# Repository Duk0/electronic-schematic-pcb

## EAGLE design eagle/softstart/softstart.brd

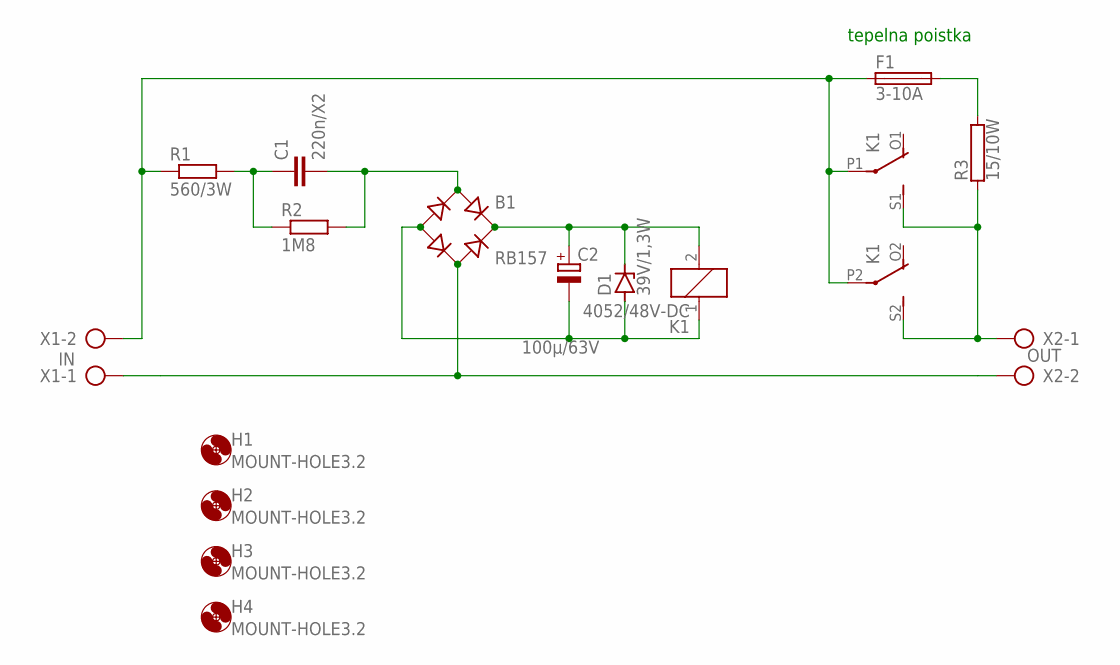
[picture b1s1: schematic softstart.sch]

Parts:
B1: RB157; RB1A
C1: 220n/X2; C150-072X183
C2: 100µ/63V; E5-10,5
D1: 39V/1,3W; DO35Z10
F1: 3-10A; TE5
H1, H2, H3, H4: MOUNT-HOLE3.2; 3,2
K1: 4052/48V-DC; F4052
R1: 560/3W; 0617/22
R2: 1M8; 0207/10
R3: 15/10W; RWM10X49
X1: IN; AK500/2
X2: OUT; AK500/2

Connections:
unnamed: B1.+, C2.+, D1.C, K1.2
unnamed: B1.-, C2.-, D1.A, K1.1
unnamed: F1.2, R3.2
unnamed: B1.AC1, C1.2, R2.2
unnamed: C1.1, R1.2, R2.1
unnamed: K1.S1 (S), K1.S2 (S), R3.1, X2.1
unnamed: F1.1, K1.P1, K1.P2, R1.1, X1.2
unnamed: B1.AC2, X1.1, X2.2

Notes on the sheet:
tepelna poistka

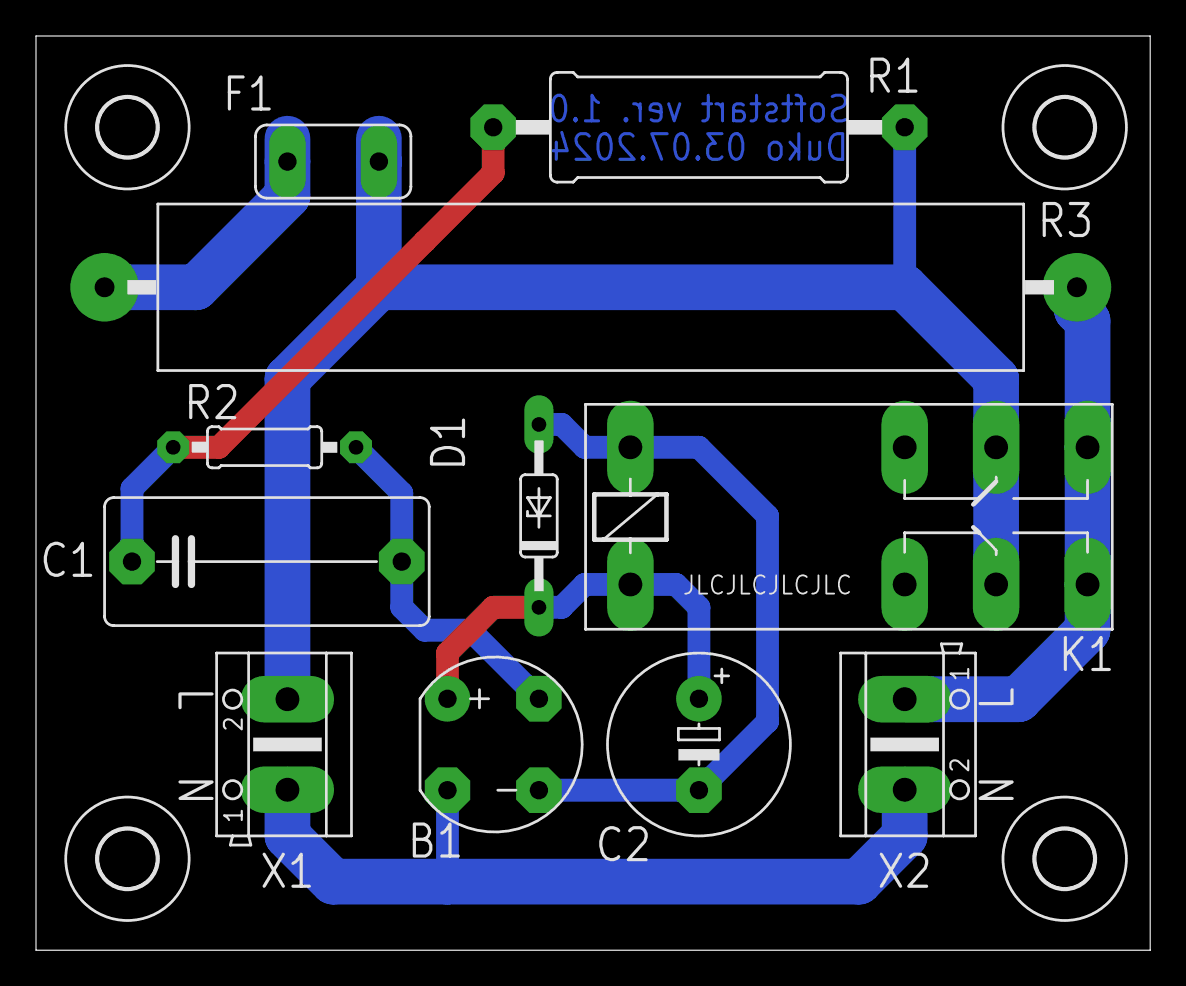
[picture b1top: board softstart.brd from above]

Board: 2 copper layers, 61.9 x 50.8 mm, 15 parts (0 on the bottom side), 8 nets.

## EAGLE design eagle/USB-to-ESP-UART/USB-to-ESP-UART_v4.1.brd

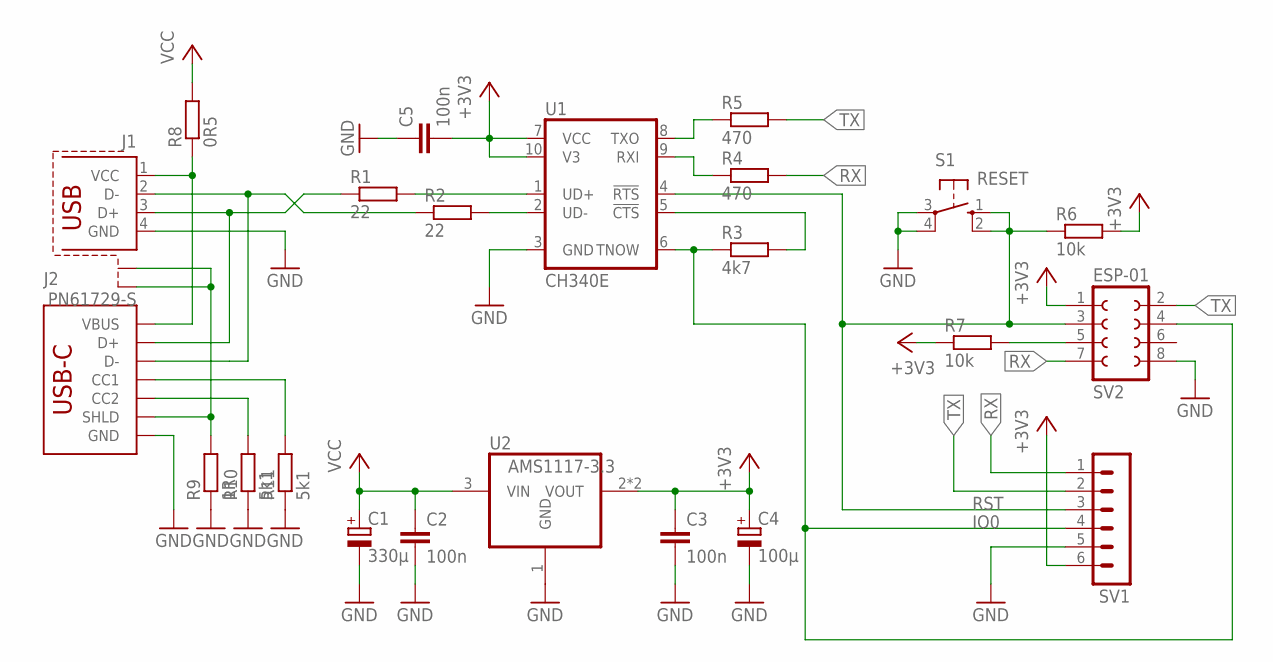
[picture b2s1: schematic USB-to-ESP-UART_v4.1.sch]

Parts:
C1: 330µ; E2,5-7
C2, C3, C5: 100n; C1206
C4: 100µ; E2,5-5
J1: PN61729-S
J2: USB_C_2-LAYER_PADS; USB-C-16P-2LAYER-PADS
R1, R2: 22; R1206
R3: 4k7; R1206
R4, R5: 470; R1206
R6, R7: 10k; R1206
R8: 0R5; R1206
R9: 1R; R1206
R10, R11: 5k1; R1206
S1: RESET; B3F-10XX
SV1: MA06-1
SV2: ESP-01; FE04-2-CL
U1: CH340E; MSOP10
U2: AMS1117-3.3; SOT223

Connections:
+3V3: C3.1, C4.+, C5.2, R6.2, R7.1, SV1.6, SV2.1, U1.7 (VCC), U1.10 (V3), U2.2 (VOUT), U2.4 (VOUT)
GND: C1.-, C2.2, C3.2, C4.-, C5.1, J1.4 (GND), J2.GND, J2.GND2 (GND), R9.1, R10.1, R11.1, S1.3, S1.4 (P1), SV1.5, SV2.8, U1.3 (GND), U2.1 (GND)
IO0: R3.1, SV1.4, SV2.4, U1.6 (TNOW)
unnamed: R3.2, U1.5 (!CTS)
unnamed: R4.1, U1.9 (RXI)
unnamed: R5.1, U1.8 (TXO)
unnamed: R1.2, U1.1 (UD+)
unnamed: R2.2, U1.2 (UD-)
unnamed: J2.B5 (CC2), R10.2
unnamed: J1.S1, J1.S2, J2.SHLD1 (SHLD), J2.SHLD2 (SHLD), J2.SHLD3 (SHLD), J2.SHLD4 (SHLD), R9.2
unnamed: J2.A5 (CC1), R11.2
unnamed: J1.2 (D-), J2.A7 (D-), J2.B7 (D-), R2.1
unnamed: J1.3 (D+), J2.A6 (D+), J2.B6 (D+), R1.1
unnamed: J1.1 (VCC), J2.VBUS1 (VBUS), J2.VBUS2 (VBUS), R8.1
unnamed: R7.2, SV2.5
RST: R6.1, S1.1 (S), S1.2 (S1), SV1.3, SV2.3, U1.4 (!RTS)
RX: R4.2, SV1.1, SV2.7
TX: R5.2, SV1.2, SV2.2
VCC: C1.+, C2.1, R8.2, U2.3 (VIN)

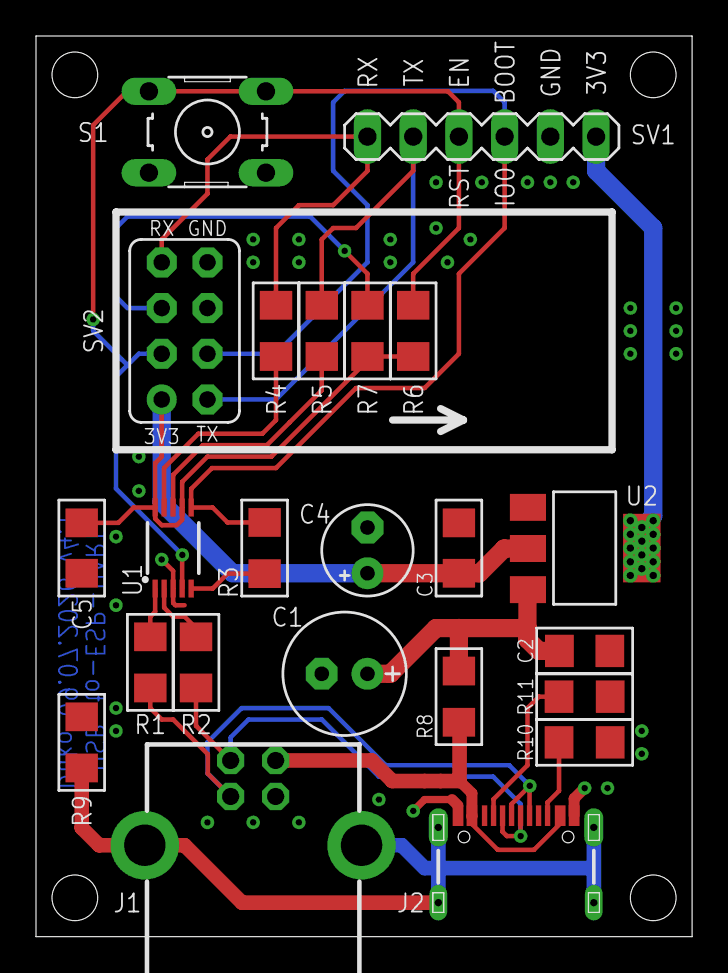
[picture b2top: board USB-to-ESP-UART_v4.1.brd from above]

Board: 2 copper layers, 36.4 x 50.0 mm, 23 parts (0 on the bottom side), 19 nets.

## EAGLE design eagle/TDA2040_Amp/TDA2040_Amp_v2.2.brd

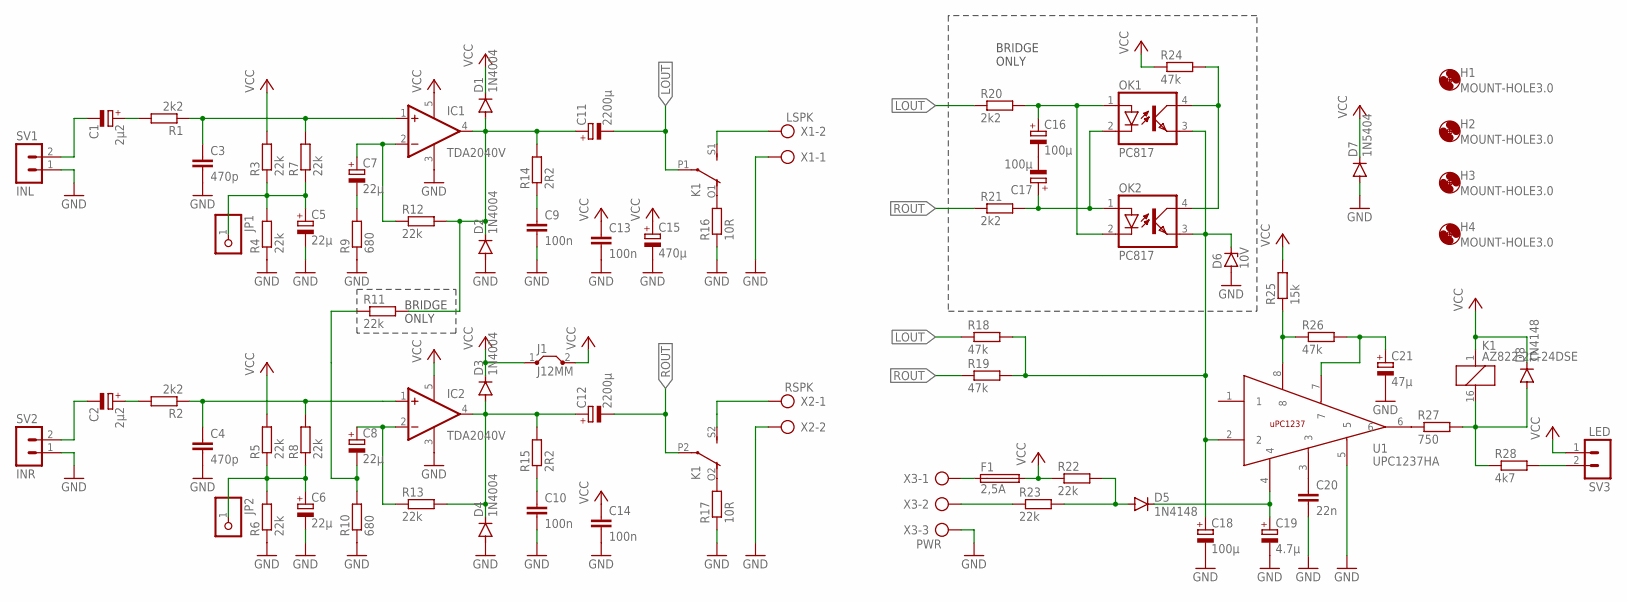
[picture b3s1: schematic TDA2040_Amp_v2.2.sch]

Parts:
C1, C2: 2µ2; E2,5-5
C3, C4: 470p; C050-024X044
C5, C6, C7, C8: 22µ; E2,5-6
C9, C10, C13, C14: 100n; C050-024X044
C11, C12: 2200µ; E5-13
C15: 470µ; E5-13
C16, C17: 100µ; E2,5-6
C18: 100µ; E2,5-5
C19: 4.7µ; E2,5-5
C20: 22n; C050-024X044
C21: 47µ; E2,5-5
D1, D2, D3, D4: 1N4004; DO41-10
D5, D8: 1N4148; DO35-7
D6: 10V; DO34Z7
D7: 1N5404; DO201-15
F1: 2,5A; SH22
H1, H2, H3, H4: MOUNT-HOLE3.0; 3,0
IC1, IC2: TDA2040V; CB360
J1: J12MM; 12
JP1, JP2: PINHD-1X1A; 1X01A
K1: AZ822-2C-24DSE; 351
OK1, OK2: PC817; DIL04
R1, R2, R20, R21: 2k2; 0207/10
R3, R4, R5, R6, R7, R8, R11, R12, R13, R22, R23: 22k; 0207/10
R9, R10: 680; 0207/10
R14, R15: 2R2; 0207/10
R16, R17: 10R; 0207/10
R18, R19, R24, R26: 47k; 0207/10
R25: 15k; 0207/10
R27: 750; 0207/10
R28: 4k7; 0207/10
SV1: INL; MA02-1
SV2: INR; MA02-1
SV3: LED; MA02-1
U1: UPC1237HA; SIP8
X1: LSPK; AK500/2
X2: RSPK; AK500/2
X3: PWR; AK500/3

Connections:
GND: C3.2, C4.2, C5.-, C6.-, C9.2, C10.2, C13.2, C14.2, C15.-, C18.-, C19.-, C20.2, C21.-, D2.A, D4.A, D6.A, D7.A, IC1.3 (V-), IC2.3 (V-), R4.1, R6.1, R9.1, R10.1, R16.1, R17.1, SV1.1, SV2.1, U1.5, X1.1, X2.2, X3.3
LOUT: C11.-, K1.P1, R18.1, R20.1
unnamed: C18.+, D6.C, OK1.3 (EMIT), OK2.3 (EMIT), R18.2, R19.2, U1.2
unnamed: C19.+, D5.C, U1.4
unnamed: R25.1, R26.1, U1.8
unnamed: C21.+, R26.2, U1.7
unnamed: C20.1, U1.3
unnamed: R27.1, U1.6
unnamed: F1.1, X3.1
unnamed: D5.A, R22.2, R23.2
unnamed: R23.1, X3.2
unnamed: D8.A, K1.16 (2), R27.2, R28.1
unnamed: K1.O2 (O), R17.2
unnamed: K1.O1 (O), R16.2
unnamed: K1.S1 (S), X1.2
unnamed: C7.+, IC1.2 (-IN), R12.1
unnamed: C11.+, D1.A, D2.C, IC1.4 (OUT), R11.2, R12.2, R14.2
unnamed: C3.1, IC1.1 (+IN), R1.1, R7.2
unnamed: C7.-, R9.2
unnamed: C5.+, JP1.1, R3.1, R4.2, R7.1
unnamed: C17.+, OK1.2 (C), OK2.1 (A), R21.2
unnamed: C9.1, R14.1
unnamed: C1.-, SV1.2
unnamed: C8.+, IC2.2 (-IN), R13.1
unnamed: C12.+, D3.A, D4.C, IC2.4 (OUT), R13.2, R15.2
unnamed: C4.1, IC2.1 (+IN), R2.1, R8.2
unnamed: C8.-, R10.2, R11.1
unnamed: C6.+, JP2.1, R5.1, R6.2, R8.1
unnamed: C10.1, R15.1
unnamed: C16.+, OK1.1 (A), OK2.2 (C), R20.2
unnamed: C2.-, SV2.2
unnamed: K1.S2 (S), X2.1
unnamed: C16.-, C17.-
unnamed: C1.+, R1.2
unnamed: OK1.4 (COL), OK2.4 (COL), R24.2
unnamed: C2.+, R2.2
unnamed: R28.2, SV3.2
ROUT: C12.-, K1.P2, R19.1, R21.1
VCC: C13.1, C14.1, C15.+, D1.C, D3.C, D7.C, D8.C, F1.2, IC1.5 (V+), IC2.5 (V+), J1.1, J1.2, K1.1, R3.2, R5.2, R22.1, R24.1, R25.2, SV3.1

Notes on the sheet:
BRIDGE ONLY

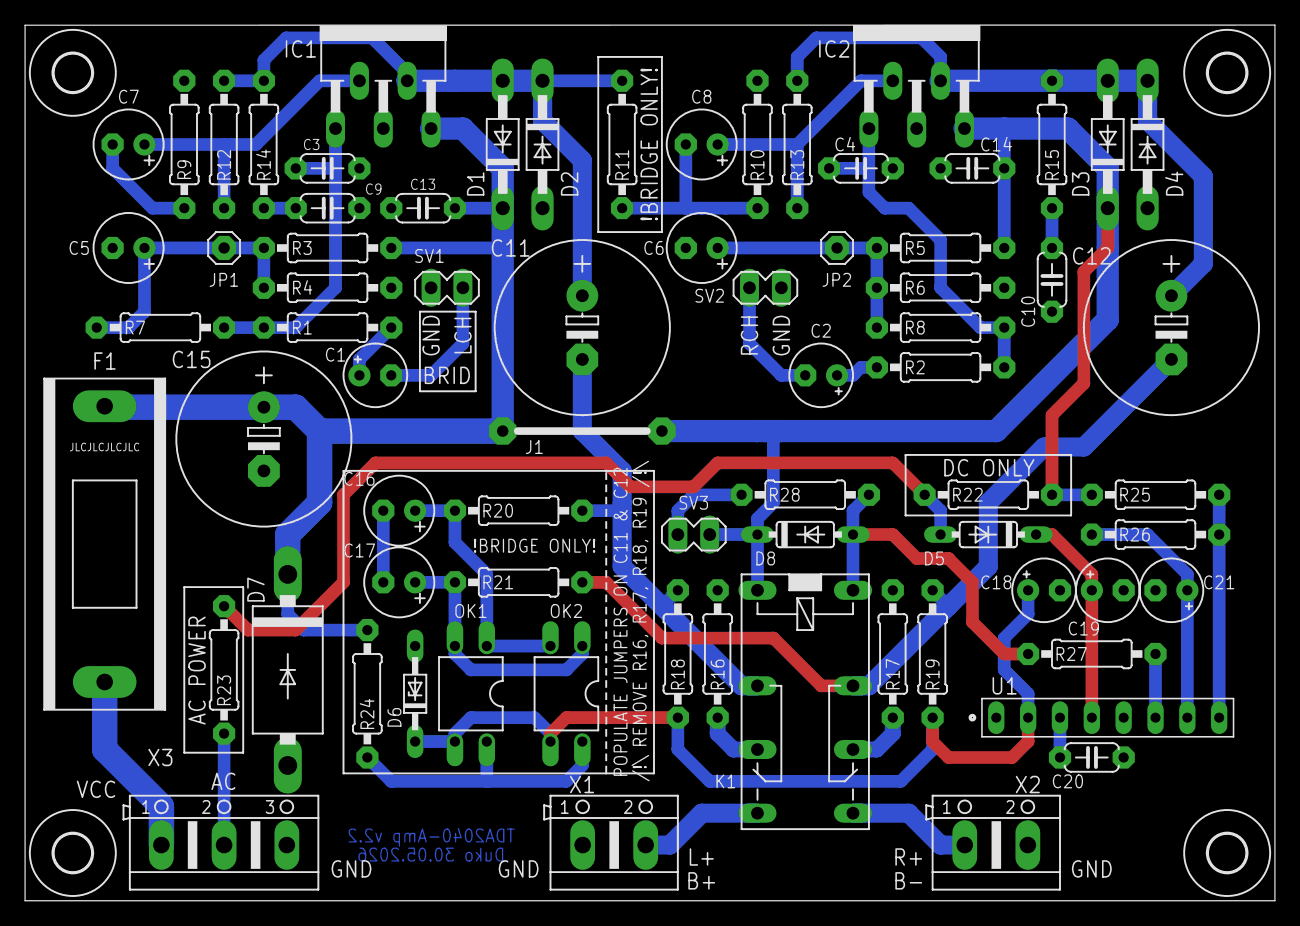
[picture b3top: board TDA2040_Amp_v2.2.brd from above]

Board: 2 copper layers, 99.7 x 69.8 mm, 77 parts (0 on the bottom side), 39 nets.

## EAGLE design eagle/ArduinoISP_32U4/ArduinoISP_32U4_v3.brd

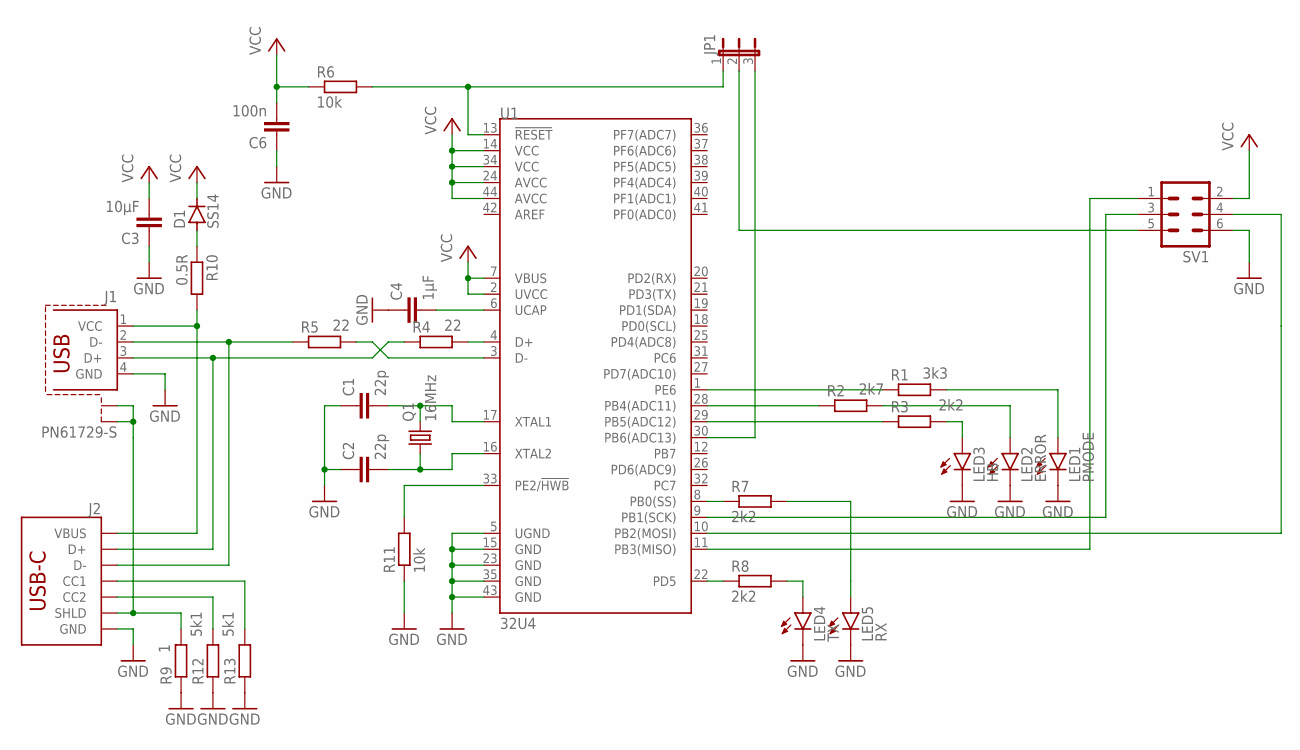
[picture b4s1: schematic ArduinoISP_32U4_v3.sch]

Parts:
C1, C2: 22p; C1206
C3: 10µF; C1206
C4: 1µF; C1206
C6: 100n; C1206
D1: SS14; DO214AC
J1: PN61729-S
J2: USB_C_2-LAYER_PADS; USB-C-16P-2LAYER-PADS
JP1: JP2E; JP2
LED1: PMODE; CHIPLED_1206
LED2: ERROR; CHIPLED_1206
LED3: HB; CHIPLED_1206
LED4: TX; CHIPLED_1206
LED5: RX; CHIPLED_1206
Q1: 16MHz; HC49UP
R1: 3k3; R1206
R2: 2k7; R1206
R3, R7, R8: 2k2; R1206
R4, R5: 22; R1206
R6, R11: 10k; R1206
R9: 1; R1206
R10: 0.5R; R1206
R12, R13: 5k1; R1206
SV1: ML6
U1: 32U4; TQFP44

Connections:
GND: C1.1, C2.1, C3.1, C4.1, C6.1, J1.4 (GND), J2.GND, J2.GND2 (GND), LED1.C, LED2.C, LED3.C, LED4.C, LED5.C, R9.1, R11.1, R12.1, R13.1, SV1.6, U1.5 (UGND), U1.15 (GND), U1.23 (GND), U1.35 (GND), U1.43 (GND)
unnamed: R5.2, U1.3 (D-)
unnamed: J1.3 (D+), J2.A6 (D+), J2.B6 (D+), R4.1
unnamed: SV1.3, U1.9 (PB1(SCK))
unnamed: C4.2, U1.6 (UCAP)
unnamed: SV1.1, U1.11 (PB3(MISO))
unnamed: SV1.4, U1.10 (PB2(MOSI))
unnamed: JP1.3, U1.30 (PB6(ADC13))
unnamed: JP1.2, SV1.5
unnamed: JP1.1, R6.2, U1.13 (!RESET)
unnamed: R2.1, U1.28 (PB4(ADC11))
unnamed: R1.1, U1.1 (PE6)
unnamed: R3.1, U1.29 (PB5(ADC12))
unnamed: LED3.A, R3.2
unnamed: LED2.A, R2.2
unnamed: LED1.A, R1.2
unnamed: C1.2, Q1.2, Q1.22 (2), U1.17 (XTAL1)
unnamed: C2.2, Q1.1, Q1.11 (1), U1.16 (XTAL2)
unnamed: R4.2, U1.4 (D+)
unnamed: J1.2 (D-), J2.A7 (D-), J2.B7 (D-), R5.1
unnamed: D1.A, R10.1
unnamed: J1.1 (VCC), J2.VBUS1 (VBUS), J2.VBUS2 (VBUS), R10.2
unnamed: R8.1, U1.22 (PD5)
unnamed: R7.1, U1.8 (PB0(SS))
unnamed: LED4.A, R8.2
unnamed: LED5.A, R7.2
unnamed: J1.S1, J1.S2, J2.SHLD1 (SHLD), J2.SHLD2 (SHLD), J2.SHLD3 (SHLD), J2.SHLD4 (SHLD), R9.2
unnamed: R11.2, U1.33 (PE2/!HWB)
unnamed: J2.B5 (CC2), R12.2
unnamed: J2.A5 (CC1), R13.2
VCC: C3.2, C6.2, D1.C, R6.1, SV1.2, U1.2 (UVCC), U1.7 (VBUS), U1.14 (VCC), U1.24 (AVCC), U1.34 (VCC), U1.44 (AVCC)

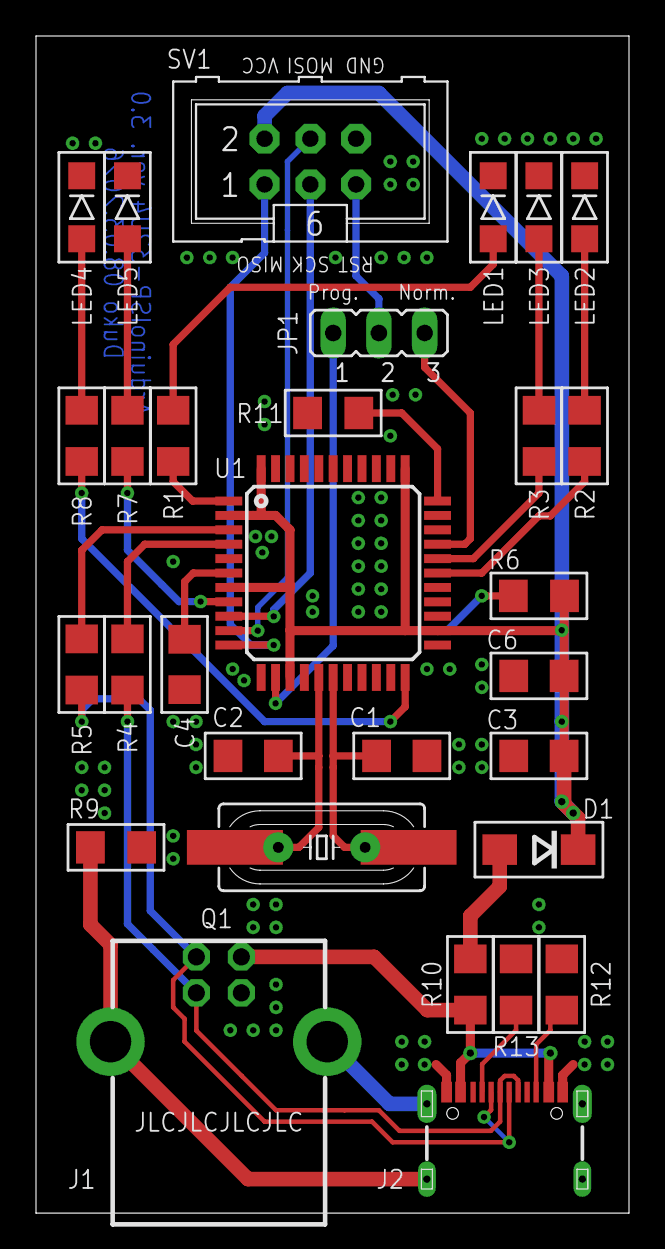
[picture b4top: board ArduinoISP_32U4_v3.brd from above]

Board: 2 copper layers, 32.9 x 65.4 mm, 30 parts (0 on the bottom side), 31 nets.

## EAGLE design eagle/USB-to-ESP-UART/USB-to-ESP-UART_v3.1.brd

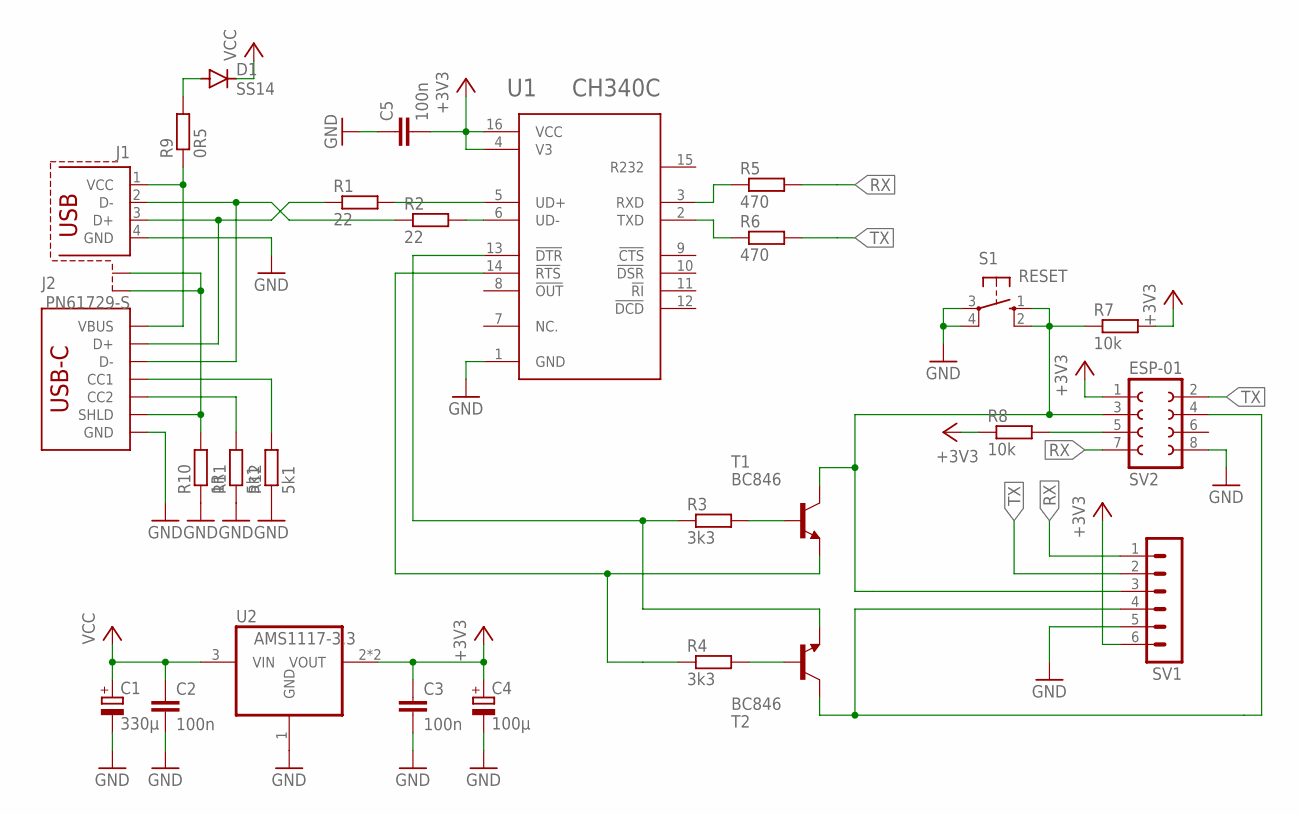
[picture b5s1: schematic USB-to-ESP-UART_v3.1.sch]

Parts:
C1: 330µ; E2,5-7
C2, C3, C5: 100n; C1206
C4: 100µ; E2,5-5
D1: SS14; DO214AC
J1: PN61729-S
J2: USB_C_2-LAYER_PADS; USB-C-16P-2LAYER-PADS
R1, R2: 22; R1206
R3, R4: 3k3; R1206
R5, R6: 470; R1206
R7, R8: 10k; R1206
R9: 0R5; R1206
R10: 1R; R1206
R11, R12: 5k1; R1206
S1: RESET; B3F-10XX
SV1: MA06-1
SV2: ESP-01; FE04-2-CL
T1, T2: BC846; SOT23-BEC
U1: CH340C; SOIC127P600X180-16N
U2: AMS1117-3.3; SOT223

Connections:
+3V3: C3.1, C4.+, C5.2, R7.2, R8.1, SV1.6, SV2.1, U1.4 (V3), U1.16 (VCC), U2.2 (VOUT), U2.4 (VOUT)
GND: C1.-, C2.2, C3.2, C4.-, C5.1, J1.4 (GND), J2.GND, J2.GND2 (GND), R10.1, R11.1, R12.1, S1.3, S1.4 (P1), SV1.5, SV2.8, U1.1 (GND), U2.1 (GND)
unnamed: R3.2, T1.B
unnamed: R4.2, T2.B
unnamed: R3.1, T2.E, U1.13 (!DTR)
unnamed: R4.1, T1.E, U1.14 (!RTS)
unnamed: R5.1, U1.3 (RXD)
unnamed: R6.1, U1.2 (TXD)
unnamed: R1.2, U1.5 (UD+)
unnamed: R2.2, U1.6 (UD-)
unnamed: R7.1, S1.1 (S), S1.2 (S1), SV1.3, SV2.3, T1.C
unnamed: J2.B5 (CC2), R11.2
unnamed: SV1.4, SV2.4, T2.C
unnamed: J1.S1, J1.S2, J2.SHLD1 (SHLD), J2.SHLD2 (SHLD), J2.SHLD3 (SHLD), J2.SHLD4 (SHLD), R10.2
unnamed: J2.A5 (CC1), R12.2
unnamed: J1.2 (D-), J2.A7 (D-), J2.B7 (D-), R2.1
unnamed: J1.3 (D+), J2.A6 (D+), J2.B6 (D+), R1.1
unnamed: J1.1 (VCC), J2.VBUS1 (VBUS), J2.VBUS2 (VBUS), R9.1
unnamed: R8.2, SV2.5
unnamed: D1.A, R9.2
RX: R5.2, SV1.1, SV2.7
TX: R6.2, SV1.2, SV2.2
VCC: C1.+, C2.1, D1.C, U2.3 (VIN)

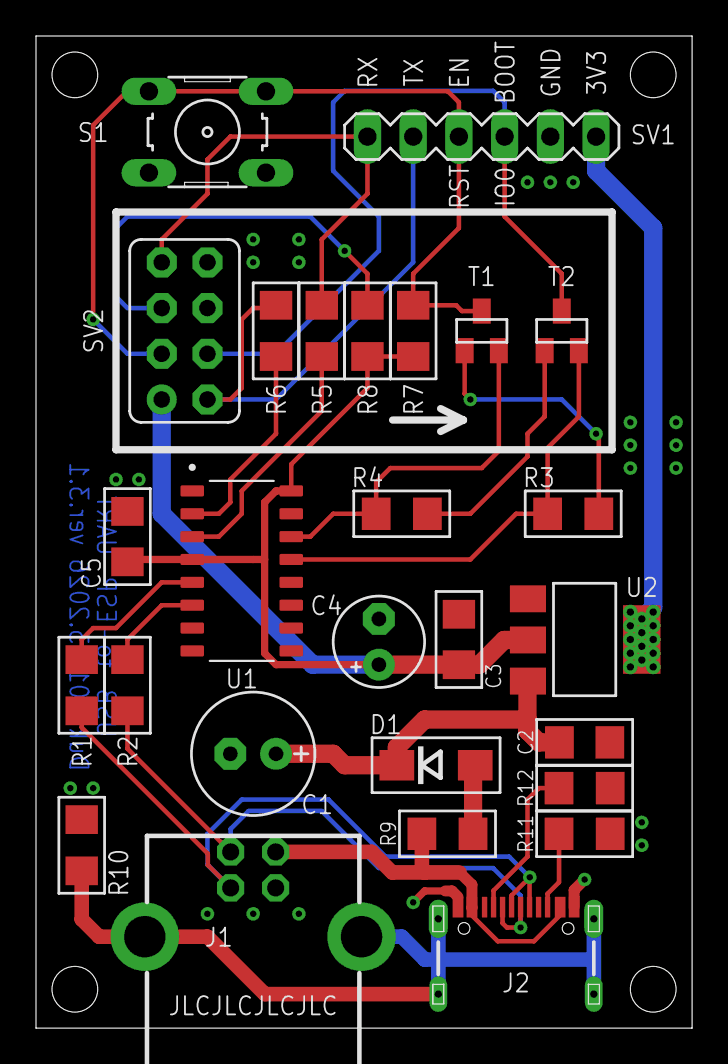
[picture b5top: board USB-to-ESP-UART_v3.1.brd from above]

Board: 2 copper layers, 36.4 x 55.1 mm, 27 parts (0 on the bottom side), 23 nets.

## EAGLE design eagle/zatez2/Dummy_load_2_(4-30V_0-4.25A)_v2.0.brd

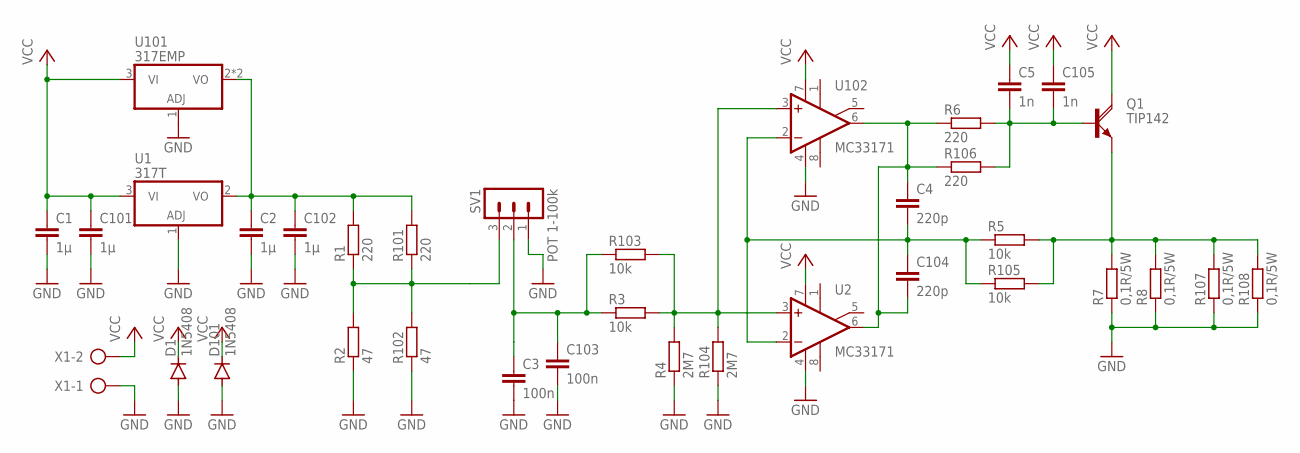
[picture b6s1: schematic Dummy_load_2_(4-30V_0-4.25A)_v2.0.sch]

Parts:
C1, C2: 1µ; C050-024X044
C3: 100n; C050-024X044
C4: 220p; C050-024X044
C5: 1n; C050-024X044
C101, C102: 1µ; C1206
C103: 100n; C1206
C104: 220p; C1206
C105: 1n; C1206
D1: 1N5408; C1702-06
D101: 1N5408; DO214AA
Q1: TIP142; SOT93V
R1, R6: 220; 0207/10
R2: 47; 0207/10
R3, R5: 10k; 0207/10
R4: 2M7; 0207/10
R7, R8: 0,1R/5W; VTA53
R101, R106: 220; R1206
R102: 47; R1206
R103, R105: 10k; R1206
R104: 2M7; R1206
R107, R108: 0,1R/5W; P0817V
SV1: POT 1-100k; MA03-1
U1: 317T; TO220H
U2: MC33171; DIL08
U101: 317EMP; SOT223
U102: MC33171; SO08
X1: AK500/2

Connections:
GND: C1.2, C2.2, C3.2, C101.2, C102.2, C103.2, D1.A, D101.A, R2.1, R4.1, R7.1, R8.1, R102.1, R104.1, R107.1, R108.1, SV1.1, U1.1 (ADJ), U2.4 (V-), U101.1 (ADJ), U102.4 (V-), X1.1
unnamed: C2.1, C102.1, R1.2, R101.2, U1.2 (VO), U101.2 (VO), U101.4 (VO)
unnamed: R1.1, R2.2, R101.1, R102.2, SV1.3
unnamed: C3.1, C103.1, R3.1, R103.1, SV1.2
unnamed: R3.2, R4.2, R103.2, R104.2, U2.3 (+IN), U102.3 (+IN)
unnamed: Q1.E, R5.2, R7.2, R8.2, R105.2, R107.2, R108.2
unnamed: C4.2, C104.1, R5.1, R105.1, U2.2 (-IN), U102.2 (-IN)
unnamed: C4.1, C104.2, R6.1, R106.1, U2.6 (OUT), U102.6 (OUT)
unnamed: C5.2, C105.2, Q1.B, R6.2, R106.2
VCC: C1.1, C5.1, C101.1, C105.1, D1.C, D101.C, Q1.C, U1.3 (VI), U2.7 (V+), U101.3 (VI), U102.7 (V+), X1.2

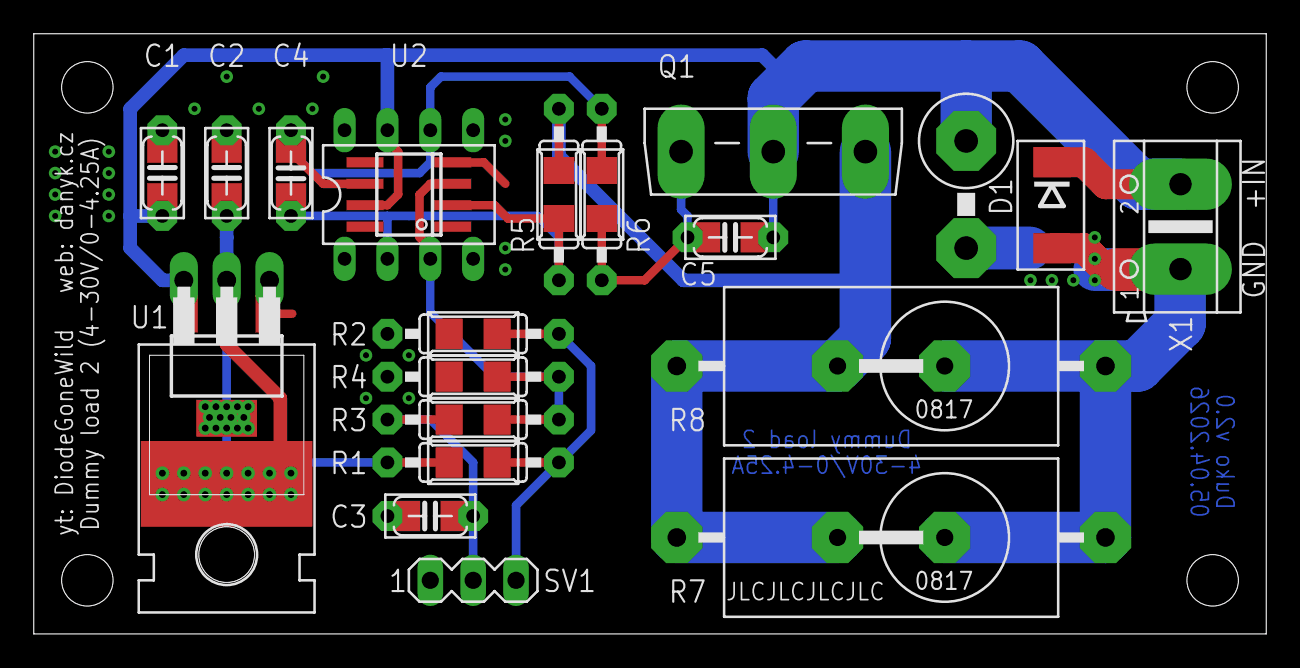
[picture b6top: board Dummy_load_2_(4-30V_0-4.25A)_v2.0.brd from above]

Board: 2 copper layers, 73.0 x 35.6 mm, 35 parts (0 on the bottom side), 10 nets.

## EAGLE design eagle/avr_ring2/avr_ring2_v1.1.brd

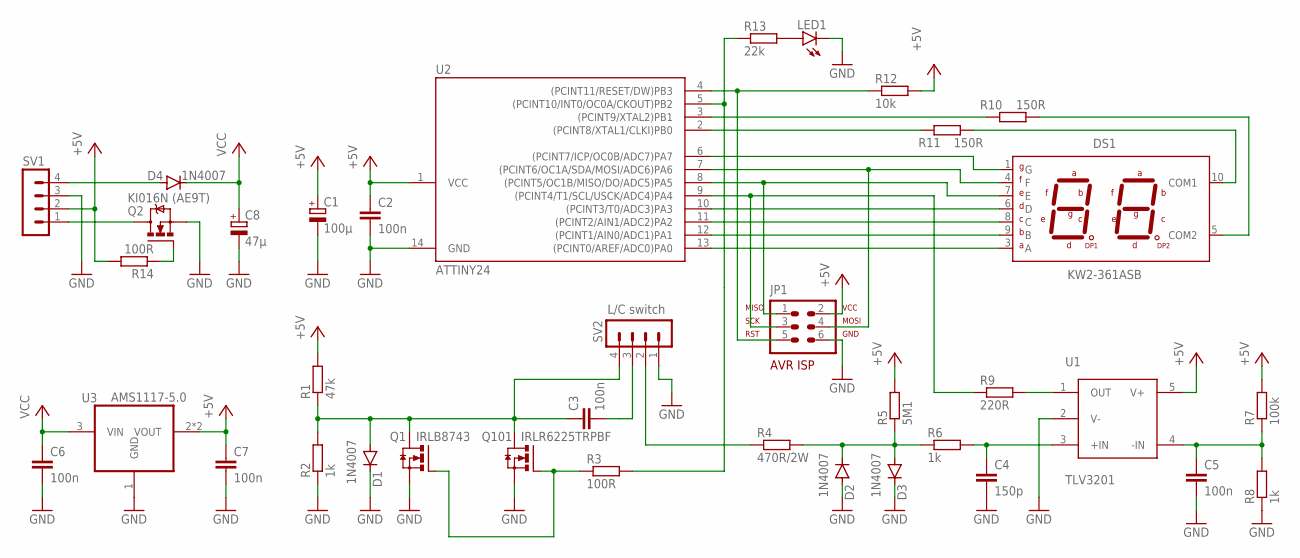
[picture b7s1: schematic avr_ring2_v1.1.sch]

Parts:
C1: 100µ; E2,5-5
C2, C5, C6, C7: 100n; C1206
C3: 100n; C102_152-062X184
C4: 150p; C1206
C8: 47µ; E2,5-5
D1, D2, D3, D4: 1N4007; DO214AC
DS1: KW2-361ASB; DA03-11SURKWA
JP1: AVR-ISP; AVR-ISP-6
LED1: LED3MM
Q1: IRLB8743; TO220AH
Q2: KI016N (AE9T); SOT23
Q101: IRLR6225TRPBF; TO-252-3
R1: 47k; R1206
R2, R6, R8: 1k; R1206
R3, R14: 100R; R1206
R4: 470R/2W; 0414/15
R5: 5M1; R1206
R7: 100k; R1206
R9: 220R; R1206
R10, R11: 150R; R1206
R12: 10k; R1206
R13: 22k; R1206
SV1: MA04-1
SV2: L/C switch; MA04-1
U1: TLV3201; SOT-23-5
U2: ATTINY24; SOIC14
U3: AMS1117-5.0; SOT223

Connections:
+5V: C1.+, C2.1, C7.1, JP1.2, R1.2, R5.2, R7.2, R12.2, R14.2, SV1.2, U1.5 (V+), U2.1 (VCC), U3.2 (VOUT), U3.4 (VOUT)
GND: C1.-, C2.2, C4.2, C5.2, C6.2, C7.2, C8.-, D1.C, D2.A, D3.C, JP1.6, LED1.K (C), Q1.E (S), Q2.2 (S), Q101.2 (S), R2.1, R8.1, SV1.3, SV2.1, U1.2 (V-), U2.14 (GND), U3.1 (GND)
unnamed: R11.1, U2.2 ((PCINT8/XTAL1/CLKI)PB0)
unnamed: R10.1, U2.3 ((PCINT9/XTAL2)PB1)
unnamed: DS1.10 (COM1), R11.2
unnamed: DS1.5 (COM2), R10.2
unnamed: DS1.3 (A), U2.13 ((PCINT0/AREF/ADC0)PA0)
unnamed: DS1.9 (B), U2.12 ((PCINT1/AIN0/ADC1)PA1)
unnamed: DS1.8 (C), U2.11 ((PCINT2/AIN1/ADC2)PA2)
unnamed: DS1.6 (D), U2.10 ((PCINT3/T0/ADC3)PA3)
unnamed: DS1.7 (E), JP1.1, U2.8 ((PCINT5/OC1B/MISO/DO/ADC5)PA5)
unnamed: DS1.4 (F), JP1.4, U2.7 ((PCINT6/OC1A/SDA/MOSI/ADC6)PA6)
unnamed: DS1.1 (G), U2.6 ((PCINT7/ICP/OC0B/ADC7)PA7)
unnamed: JP1.3, R9.1, U2.9 ((PCINT4/T1/SCL/USCK/ADC4)PA4)
unnamed: R9.2, U1.1 (OUT)
unnamed: C5.1, R7.1, R8.2, U1.4 (-IN)
unnamed: C4.1, R6.2, U1.3 (+IN)
unnamed: D2.C, D3.A, R4.2, R5.1, R6.1
unnamed: JP1.5, R12.1, U2.4 ((PCINT11/RESET/DW)PB3)
unnamed: Q1.B (G), Q101.1 (G), R3.1
unnamed: LED1.A, R13.2
unnamed: D4.A, SV1.4
unnamed: C3.2, C3.3 (2), SV2.3
unnamed: R4.1, SV2.2
unnamed: C3.1, D1.A, Q1.C (D), Q101.3 (D), R1.1, R2.2, SV2.4
unnamed: R3.2, R13.1, U2.5 ((PCINT10/INT0/OC0A/CKOUT)PB2)
unnamed: Q2.3 (D), SV1.1
unnamed: Q2.1 (G), R14.1
VCC: C6.1, C8.+, D4.C, U3.3 (VIN)

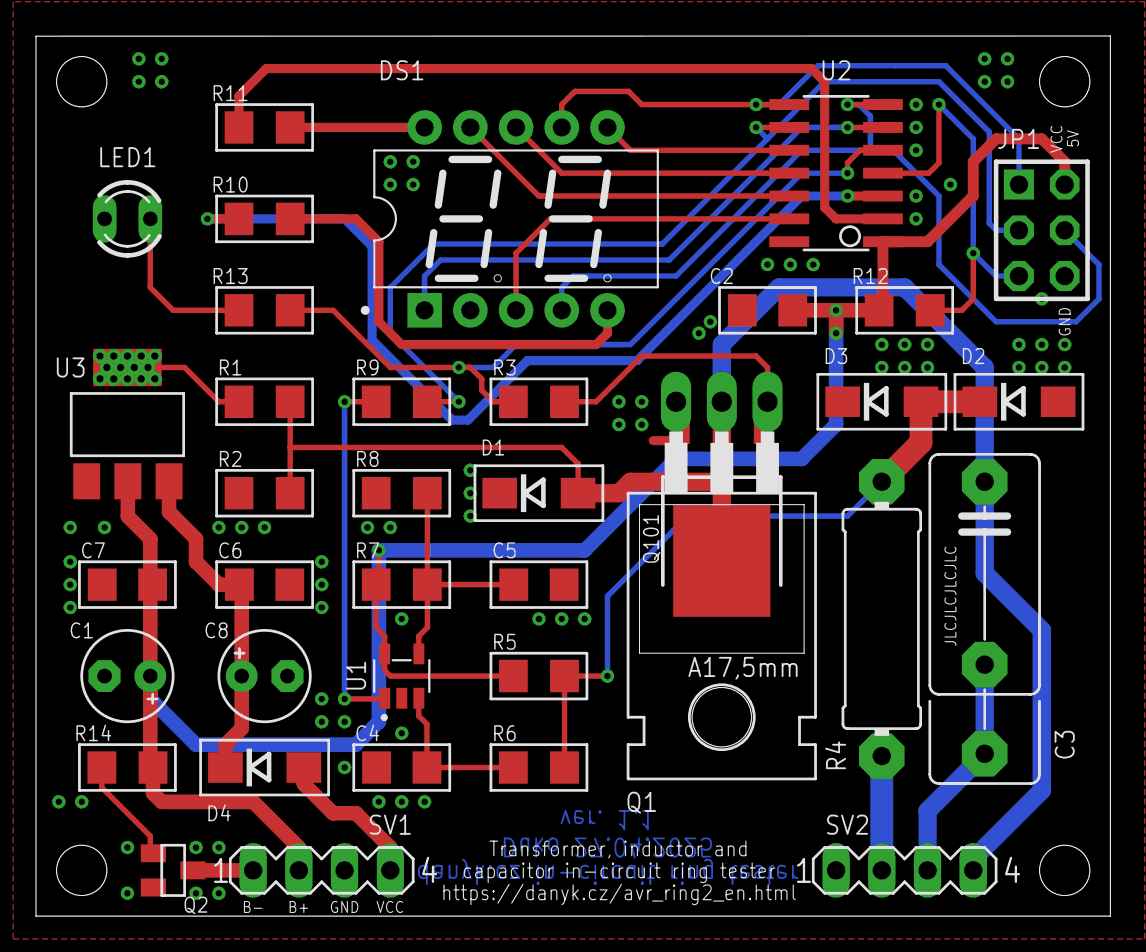
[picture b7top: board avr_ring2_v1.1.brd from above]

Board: 2 copper layers, 59.7 x 48.9 mm, 37 parts (0 on the bottom side), 29 nets.

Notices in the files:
parts and their libraries:
SparkFun-IC-Microcontroller: Licensing: Creative Commons ShareAlike 4.0 International - https://creativecommons.org/licenses/by-sa/4.0
